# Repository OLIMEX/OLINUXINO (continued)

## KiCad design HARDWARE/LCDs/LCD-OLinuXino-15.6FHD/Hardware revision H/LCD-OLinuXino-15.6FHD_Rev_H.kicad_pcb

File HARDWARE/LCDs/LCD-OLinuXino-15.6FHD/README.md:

# LCD-OLinuXino-15.6FHD

Full HD 15.6 inch display without touchscreen

# Overview

A Full HD (1920x1080) display compatible with A10 and A20 boards.
Due to its high power demand the display is provided with a separate 5V power jack.
Note that it would not work properly with A13 or A10s boards which lack the computational power required for a smooth operation.

# Features

- LCD display 1920x1080 pixels
- 3.5W power consumption
- 15.6”(15.55”)
- HD 16:9 color TFT-LCD with LED backlight
- Works with the more powerful OLinuXino and SOM designs
- Two interface connectors: both 40 pin 0.1" pitch and 40 pin 0.05" pitch
- **Note that the cable to connect to your board and the additional power adapter are sold separately**

# Documents

- [Display datasheet](doc/datasheets/OLIMEX-TFT-LCD-N156HGE-LG1-ver-1-0.pdf)

# Hardware

- [Source files](.)
- [Olimex product page](https://www.olimex.com/Products/OLinuXino/LCD/LCD-OLinuXino-15.6FHD/open-source-hardware)

# FAQ

### What is the difference between LCD-OLinuXino-15.6 and LCD-OLinuXino-15.6FHD?

The dot pitch is different.
The native resolution of LCD-OLinuXino-15.6 is 1366x768.
The native resolution of LCD-OLinuXino-15.6FHD is 1920x1080.

### Which boards can be used with LCD-OLinuXino-15.6FHD?

OLinuXino boards that carry the OLinuXino or SOM name and have an LCD connector would work with the LCD-OLinuXino-15.6FHD.
Unlike the previous iteration of displays, the LCD-OLinuXino-15.6FHD has both 0.1" connector and 0.05" connector on its back.
This allows the easy connection of boards with big LCD connector and also of boards with small LCD connector (like the LIME boards).
You only need a single 40-40 cable with the same step on both sides to connect between the LCD and the board.
Please note that the 15.6 inch display is not recommended for boards with Allwinner A13 or A10s since these boards migth lack the required computing power for a smooth operation (especially under Android).

### I bought LCD-OLinuXino-15.6FHD but when I connect it to the A20-OLinuXino I receive no image on the display. What do I do wrong?

The default A20-OLinuXino image is set for a HDMI display and 720p resolution.
LCD-OLinuXino-15.6FHD has a native resolution of 1920 x 1080 pixels.
To use LCD with A20-OLinuXino you need to set proper video output settings.
Explanation of how to do it can be found at [this wiki article of the A20 board](https://www.olimex.com/wiki/A20-OLinuXino-MICRO#How_to_change_HDMI.2C_VGA_and_LCD_resolutions_in_the_official_Debian_image.3F).

### I bought LCD-OLinuXino-15.6FHD and the SD card that has Linux image written on it. However the resolution I see on my VGA/LCD is not correct. What am I missing?

You would need to change the video output setting using the shell script.
Type: ``./change_display`` and then press **Tab** to auto-complete and press **Enter**.
Navigate to the LCD category and select **1920 x 1080 pixels**.

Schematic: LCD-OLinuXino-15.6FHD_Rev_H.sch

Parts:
C1, C2: 1uF; C_0603_5MIL_DWS
C3, C4, C5, C6, C7, C8, C9, C11, C13, C14, C15, C16, C17, C18, C19, C24: 100nF; C_0402_5MIL_DWS
C10, C12: 33pF; C_0402_5MIL_DWS
C20, C21: 1uF/50V; C_0805_5MIL_DWS
D1, D3: SS34; SMB-KA
D2: BAT54C; SOT23
FB1, FB2, FB3: FB0805; L_0805_5MIL_DWS
FB4: (na) FB0805; L_0805_5MIL_DWS
FET1: IRLML6402; SOT23
IC1: PIC10F206-I/OT; SOT23-6
L1: CL22uH / YS75; SD75
LIME1, LIME2: ML40-GPH127SMT-0X20; GPH127SMT-02X20(PA-V16X-2X20-LF)
P1: CONN_01X40; FPV-WZA21-40-LF
P2: ICSP
PWR1: 5 .. 16V DC; PWR-JACK-MIL-SMT
Q1: 4SB24.000F20E15/5x3.2mm/20ppm/20pF; Q5x3.25
R1, R2, R3, R4, R10: 2.2K; R_0402_5MIL_DWS
R5, R6, R8: 10K; R_0402_5MIL_DWS
R11: 10K; R0402
R12, R15: (na) 100K; R0402
R13: 20K 1%; R_0603_5MIL_DWS
R14: 1.05K 1%; R_0603_5MIL_DWS
RM1: (na); R_MATRIX_4_KICAD
SOM204-LVDS1: FPV-WZA21-40-LF
T1: DTC114YKA(SOT-23); SOT23
U1: MCP1700-1202; SOT89
U2: NCS8801; QFN56_7x7mm_0.4p
U3: MT3608; SOT23-6
eDP1: LCD_CONN; eDP-TERES
uICR1: ML40-GBH-254-SMT-40; GBH-254-SMT-40

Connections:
+1V2: C2.1, C11.1, C17.1, FB2.1, U1.3 (Vo), U2.52 (DVDD12)
+3V3: C1.1, C14.1, C18.1, C24.1, FB1.1, FB3.1, FET1.3, IC1.5, P2.2, R2.1, R5.2, R6.2, R11.1, R15.1, U1.2 (Vi), U2.47 (DVDD33), U2.51 (CSB), U2.55 (I2CSEL), eDP1.1, eDP1.2
/+3.3V: C3.1, FET1.2, LIME1.4, LIME2.3, P1.3, R8.1, SOM204-LVDS1.3, U2.14 (HSVDD33), uICR1.3
/CLK_EDIE: LIME1.30, LIME2.29, SOM204-LVDS1.29, uICR1.29
/CTP_INT: LIME1.38, LIME2.37, RM1.4, SOM204-LVDS1.37, uICR1.37
/D20: LIME1.10, LIME2.9, SOM204-LVDS1.9, uICR1.9
/D21: LIME1.9, LIME2.10, SOM204-LVDS1.10, uICR1.10
/DAT_EDID: LIME1.29, LIME2.30, SOM204-LVDS1.30, uICR1.30
/DCR_EN: LIME1.32, LIME2.31, SOM204-LVDS1.31, uICR1.31
/DP1_N: C5.1, U2.37 (DPO1_N)
/DP1_P: C4.1, U2.38 (DPO1_P)
/DPA_N: C8.1, U2.34 (DPAUX_N)
/DPA_P: C9.1, U2.33 (DPAUX_P)
/DPO_N: C7.1, U2.35 (DPO0_N)
/DPO_P: C6.1, U2.36 (DPO0_P)
/EDP_AUX_N: C8.2, R15.2, eDP1.5
/EDP_AUX_P: C9.2, R12.2, eDP1.4
/EDP_LANE0_N: C6.2, eDP1.8
/EDP_LANE0_P: C7.2, eDP1.7
/EDP_LANE1_N: C4.2, eDP1.11
/EDP_LANE1_P: C5.2, eDP1.10
/GPIO0: LIME1.34, LIME2.33, SOM204-LVDS1.33, uICR1.33
/GPIO1: LIME1.33, LIME2.34, SOM204-LVDS1.34, uICR1.34
/HPD: IC1.6, P1.33, P2.1, R10.1, RM1.5
/HSYNC: P1.29, U2.2 (HSYNC)
/IMG_EN: LIME1.31, LIME2.32, SOM204-LVDS1.32, uICR1.32
/IRES: D2.2 (A), IC1.4, R4.2
/LCD_B0: P1.21, U2.28 (D0)
/LCD_B1: P1.22, U2.27 (D1)
/LCD_B2: P1.23, U2.26 (D2)
/LCD_B3: P1.24, U2.25 (D3)
/LCD_BKL: LIME1.35, LIME2.36, P1.36, SOM204-LVDS1.36, eDP1.15, uICR1.36
/LCD_CLK: P1.31, U2.3 (PCLK)
/LCD_DE: P1.32, U2.56 (DE)
/LCD_PWRE: LIME1.36, LIME2.35, P1.35, SOM204-LVDS1.35, T1.1 (B), uICR1.35
/LVDIE0_N: LIME1.15, LIME2.16, P1.18, SOM204-LVDS1.16, U2.15 (LVDIE0_N), uICR1.16
/LVDIE0_P: LIME1.16, LIME2.15, P1.17, SOM204-LVDS1.15, U2.16 (LVDIE0_P), uICR1.15
/LVDIE1_N: LIME1.17, LIME2.18, P1.16, SOM204-LVDS1.18, U2.17 (LVDIE1_N), uICR1.18
/LVDIE1_P: LIME1.18, LIME2.17, P1.15, SOM204-LVDS1.17, U2.18 (LVDIE1_P), uICR1.17
/LVDIE2_N: LIME1.19, LIME2.20, P1.14, SOM204-LVDS1.20, U2.19 (LVDIE2_N), uICR1.20
/LVDIE2_P: LIME1.20, LIME2.19, P1.13, SOM204-LVDS1.19, U2.20 (LVDIE2_P), uICR1.19
/LVDIE3_N: LIME1.7, LIME2.8, P1.26, SOM204-LVDS1.8, U2.23 (LVDIE3_N), uICR1.8
/LVDIE3_P: LIME1.8, LIME2.7, P1.25, SOM204-LVDS1.7, U2.24 (LVDIE3_P), uICR1.7
/LVDIEC_N: LIME1.5, LIME2.6, P1.28, SOM204-LVDS1.6, U2.21 (LVCIE_N), uICR1.6
/LVDIEC_P: LIME1.6, LIME2.5, P1.27, SOM204-LVDS1.5, U2.22 (LVCIE_P), uICR1.5
/LVDIO0_N: LIME1.21, LIME2.22, P1.12, SOM204-LVDS1.22, U2.4 (LVDIO0_N), uICR1.22
/LVDIO0_P: LIME1.22, LIME2.21, P1.11, SOM204-LVDS1.21, U2.5 (LVDIO0_P), uICR1.21
/LVDIO1_N: LIME1.23, LIME2.24, P1.10, SOM204-LVDS1.24, U2.6 (LVDIO1_N), uICR1.24
/LVDIO1_P: LIME1.24, LIME2.23, P1.9, SOM204-LVDS1.23, U2.7 (LVDIO1_P), uICR1.23
/LVDIO2_N: LIME1.25, LIME2.26, P1.8, SOM204-LVDS1.26, U2.8 (LVDIO2_N), uICR1.26
/LVDIO2_P: LIME1.26, LIME2.25, P1.7, SOM204-LVDS1.25, U2.9 (LVDIO2_P), uICR1.25
/LVDIO3_N: LIME1.13, LIME2.14, P1.20, SOM204-LVDS1.14, U2.12 (LVDIO3_N), uICR1.14
/LVDIO3_P: LIME1.14, LIME2.13, P1.19, SOM204-LVDS1.13, U2.13 (LVDIO3_P), uICR1.13
/LVDIOC_N: LIME1.27, LIME2.28, P1.6, SOM204-LVDS1.28, U2.10 (LVCIO_N), uICR1.28
/LVDIOC_P: LIME1.28, LIME2.27, P1.5, SOM204-LVDS1.27, U2.11 (LVCIO_P), uICR1.27
/NCS_RES: C19.1, D2.3 (K), LIME1.37, LIME2.38, R4.1, RM1.3, SOM204-LVDS1.38, U2.46 (RSTB), uICR1.38
/PIC_RES: P1.37, R10.2, R11.2
/RES: D2.1 (A), P1.34, RM1.6
/SCL: IC1.3, P1.39, P2.5, R6.1, RM1.7, U2.53 (SCL)
/SDA: IC1.1, P1.40, P2.4, R5.1, RM1.8, U2.54 (SDA)
/TWI_SCL: LIME1.40, LIME2.39, RM1.2, SOM204-LVDS1.39, uICR1.39
/TWI_SDA: LIME1.39, LIME2.40, RM1.1, SOM204-LVDS1.40, uICR1.40
/VLEDS: C21.1, D1.1 (K), FB4.2, R13.1, eDP1.21, eDP1.22
/VLED_EN: LIME1.12, LIME2.11, R2.2, SOM204-LVDS1.11, eDP1.14, uICR1.11
/VPWM_EN: LIME1.11, LIME2.12, SOM204-LVDS1.12, uICR1.12
/VSINK: P1.30, U2.1 (VSYNC)
GND: C1.2, C2.2, C3.2, C10.2, C11.2, C12.2, C13.2, C14.2, C15.2, C16.2, C17.2, C18.2, C19.2, C20.2, C21.2, C24.2, IC1.2, LIME1.1, LIME1.3, LIME2.2, LIME2.4, P1.2, P1.4, P1.P1, P1.P2, P2.3, PWR1.2 (-), PWR1.3 (-), R1.1, R12.1, R14.2, SOM204-LVDS1.0, SOM204-LVDS1.2, SOM204-LVDS1.4, T1.2 (E), U1.1 (GND/ADJ), U2.0 (THERMAL), U2.49 (MOSI), U2.50 (SCK), U3.2 (GND), eDP1.0, eDP1.3, eDP1.6, eDP1.9, eDP1.12, eDP1.19, eDP1.20, uICR1.2, uICR1.4
unnamed: C10.1, Q1.1, U2.30 (XTALOUT)
unnamed: C12.1, Q1.2, U2.29 (XTALIN)
unnamed: C13.1, FB1.2, U2.31 (XVDD33)
unnamed: C15.1, FB2.2, U2.43 (AVDD12)
unnamed: C16.1, FB3.2, U2.32 (AVDD33)
unnamed: D1.2 (A), L1.2, U3.1 (OUT)
unnamed: FET1.1, R3.2, R8.2
unnamed: R1.2, U2.45 (PWD)
unnamed: R3.1, T1.3 (C)
unnamed: R13.2, R14.1, U3.3 (FB)
VDD: C20.1, D3.1, FB4.1, L1.1, PWR1.1 (+), U3.4 (EN), U3.5 (IN)

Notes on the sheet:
All lanes impedance 100ohm inter-pair skew < 50mils
eDP
pwm
RGB888
LVDS

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
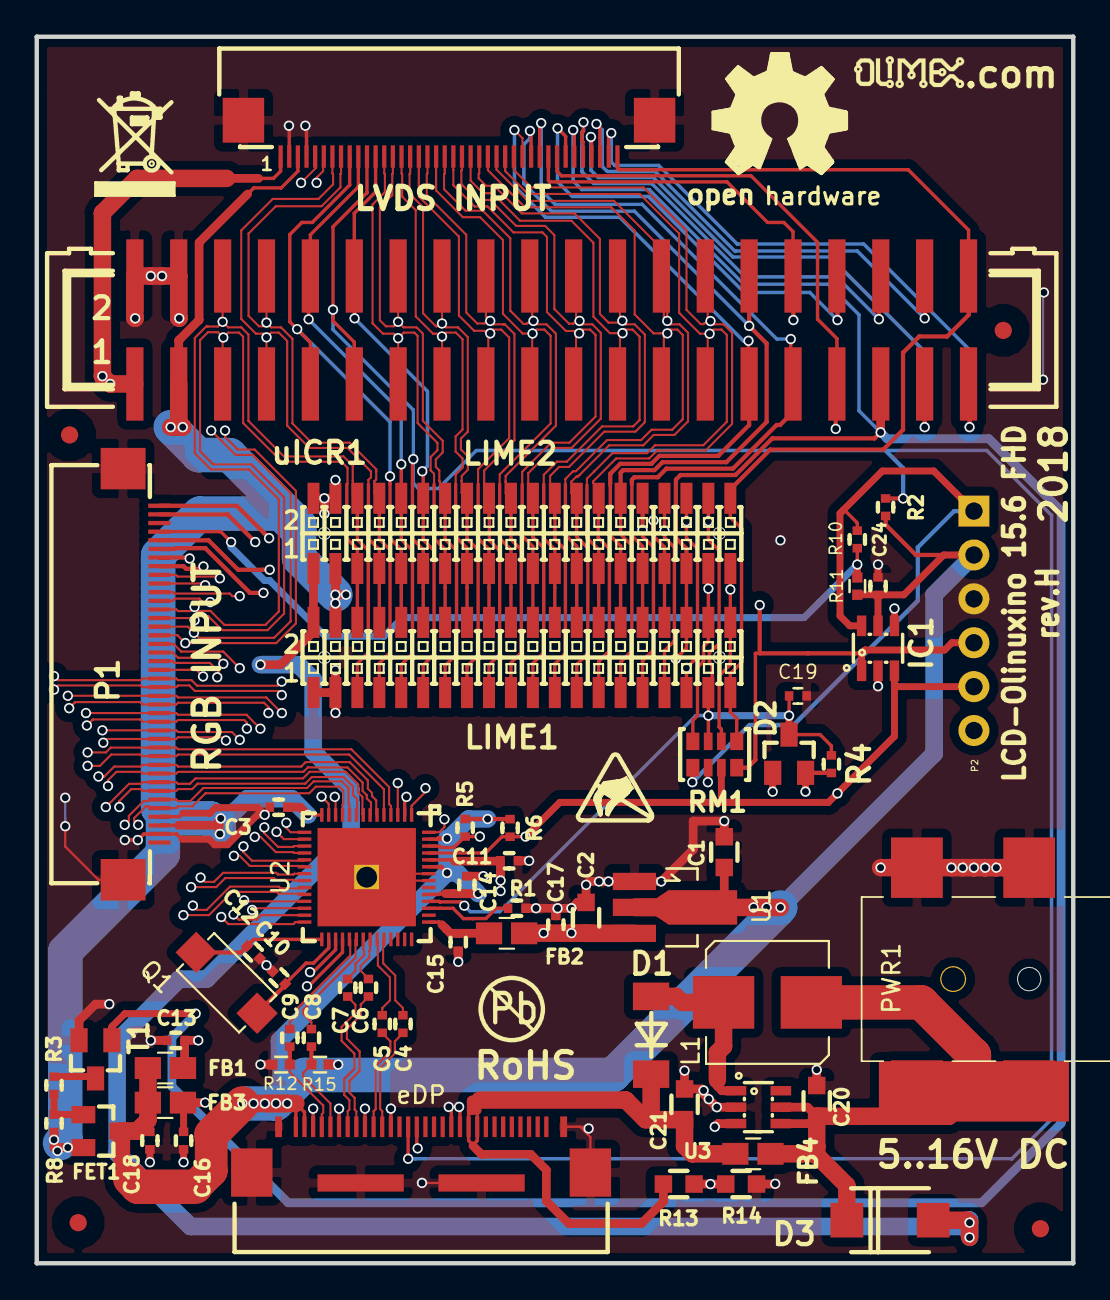
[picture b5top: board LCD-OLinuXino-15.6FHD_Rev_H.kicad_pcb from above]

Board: 4 copper layers, 60.0 x 71.0 mm, 60 parts (0 on the bottom side), 79 nets.

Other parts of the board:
Ref**: Val**; LOGO_ANTISTATIC_SMALL_4.5mmX2.8mm

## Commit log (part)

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2013-08-23 A10-A20-OLinuXino-MICRO REV.C and D
2013-09-05 add video encoding and decoding demo
2013-09-06 iMX233-OLinuXino-NANO CAD files
2013-10-02 Android A20-OLinuXino-TOOLS
2013-10-03 add voice to OLinuXino
2013-10-04 A13-OLinuXino PDF was not searchable
2013-11-23 updated iMX233-OLinuXino-MAXI CAD files to Rev.C2
2013-11-25 Micro schematics in wrong folders.
    Micro revision C in Maxi folders. Needs to be deleted. Lub/OLIMEX
2014-01-21 A10-OLinuXino-LIME REV.B and GPIO description
2014-02-13 A10-OLinuXino-LIME shield templates
2014-02-18 A20-OLinuXino-MICRO REV.E2 upload
2014-04-23 Update DEBIAN-BUILD.txt
    Boot was hanging because terminal in /etc/inittab was ttyAM0 instead of ttyAMA0. Tested on imx nano.
2014-05-27 MOD-IRDA+ code for home automation with OLinuXino
2014-06-18 A10-LIME board revision C files updated
    A10-LIME schematic, board layout and pdf added
2014-07-07 I2C EXAMPLE - MOD-RTC and A20-OLINUXINO-MICRO
    An example of A20-OLINUXINO-MICRO and a RTC module that gets connected
    to the UEXT. Full instructions in the README_RTC_A20.txt
2014-07-23 SPI EXAMPLE - MOD-LCD3310 and A20-OLINUXINO-MICRO
    A demo with detailed description on using the hardware SPI under Debian.
2014-07-25 MOD-RGB firmware 3 demo with A20-OLINUXINO-MICRO
    Detailed instructions might be found in the README.txt file.
2014-07-25 A20 demo examples
2014-07-25 A20 demo examples
    Fixed few paths
2014-08-22 Add Android Jelly Bean build for A13-OLinuXino-WIFI
2014-09-04 Python packages for OLinuXino boards
2014-09-17 iMX233-MICRO revision D files
2014-09-20 Create A20-TOOLS
2014-10-02 A20-OLinuXino-LIME2 hardware sources added
2014-10-23 Added A13 sources
2014-10-24 RT5350F-OLinuXino first prototypes
2014-11-12 Files and description on A20 image compilation
2014-11-14 Torrent to the A20 filesystem
2014-11-19 Formatting improvement of GPIO table for LIME2
2014-12-11 A20-OLinuXino-LIME separated in own folder
2014-12-16 Adding dragon face
2014-12-18 Updated readme of the example
2014-12-23 To load in git formatting
2014-12-23 Updated links to resources need for A20 Debian
2014-12-23 Revert "Update README.txt"
    This reverts commit 9d136c74a2f802c392218a2b047997fe4ff03f86.
2014-12-23 Formatting changes
2014-12-23 Fixed a misleading command in the building doc
2015-01-08 Links to resources updated!
2015-02-24 A13-OLINUXINO files revision G
2015-03-13 revisions
2015-03-16 Updated a number of schematics
2015-03-19 rk3188 datasheet
2015-03-25 Update README.txt
    Modified README( Fixed typo).
2015-04-22 Fix tx DMAs address typo
    This typo cause to hang spidev2 on transfer data in DMA mode.
2015-05-18 RT5350F-OLinuXino update
2015-05-26 RT5350F-OLinuXino-B update
2015-05-27 MOD-IO2 tool
    tool that simplifies the usage of MOD-IO2
2015-05-27 MOD-IO2 Linux tool additional info
2015-05-27 MOD-IO2 Linux tool update
2015-05-27 MOD-IO2 Linux tool
2015-05-28 relay example mod-io2
2015-05-28 MOD-IO2 simple example
2015-05-28 MOD-IO example
2015-05-29 Update to add pwm function
2015-05-29 Update of the pwm function
2015-06-03 Correction of web address
    Correction of small typo in web address.
2015-06-05 Add R8M datasheet
2015-06-09 a13 build description
2015-06-09 torrent
2015-06-09 added build description
2015-06-11 updated readme.txt
2015-06-15 Fix pyA20 gpio1 connector constants
    In definition of gpio1 connector mapping constant there is a "cut&paste" error which prevent access to port pins.
2015-06-19 Add C++ library for GPIOs
2015-06-30 pyA13 increased minor revision
2015-07-06 Updated olinuxino-rt5350 firmware image
2015-08-15 Initial version adding eMMC support
    This commit creates a rev D board with an optional eMMC variant for
    storage.
    Some notes:
    The eMMC chip generally handles the state internally when enabling
    4 or 8 bit data modes. So having the spare data lines connected to
    NDQ[4:7] should be no problem. This needs to be tested however and
2015-08-17 Updated system images
2015-08-17 Fixed typo
2015-08-23 Re-route Sata power enable pins
    With this patch, we re-route the sata power enable pins around to avoid
    being in the NAND flash area, potentially freeing up space for other
    purposes (eMMC) here.
    This patch unfortunately has some noise in it (diff-ing eagle files is
    hard)
    Noise 1: Started to use eagle 7.2
2015-08-23 Move sata lines slightly north to make more room below the NAND flash
2015-08-23 Rename R28 to NAND_WP
    R28 is a spot where a zero ohm resistor can be placed to control the
    NAND flash's Write Protect. This commit renames this resistor to NAND_WP
    and marks it as such on the silk-screen.
2015-08-24 Updated release image
2015-11-02 New builds
    Jessie build instructions
2015-11-04 New defconfig
2015-11-04 Update instructions
2015-11-10 Added change display script
    For reference only, it is also inside the file system, no need to
    download it separately.
2015-11-10 Fixed RT5350 issue with repeating MAC address
2015-11-10 RT5350 README updated
2015-11-13 H3-OLinuXino prototype CAD files and H3 SoC datasheet
2015-11-17 A33-OLinuXino first prototypes update CAD files
2015-11-20 A64-OLinuXino component placement, all components libraries updated
2016-01-03 Fixed minor detail in fdisk commands
2016-01-07 Update
    Fixed bug in GPIO3 and GPIO4
2016-01-22 A64-OLinuXino routing completed
2016-01-29 Revision C
    Minor changes mainly on the I2C lines (set to hardware I2C).
2016-03-03 Added image for RT5350F-OLinuXino-DIN
2016-04-08 New A20 releases
2016-04-08 Link to FS torrent
2016-04-11 Update
    Incorrect bit swap
2016-04-20 Fixes raw downloads
    The script.bin and uEnv.txt files should be downloaded raw;
    the current wget command downloads the HTML page instead of the desired file.
2016-04-20 Incorrect copy command
    At this point the file is called `uEnv.txt`, not `uEnv.txt.bin`
2016-06-17 Updated instructions
    Build description updated, RAM now 384MHz to improve stability.
2016-06-17 Update
    Added examples for MOD-IO2 and MOD-LED8x8RGB
2016-06-17 Renamed README file
2016-06-17 Update
    Removed duplicate folder for the MOD-IO2 example (the other one is
    located inside UEXT-MODULES folder)
2016-06-23 A20-OLinuXino-LIME2 Rev. F and Rev.G update
2016-07-05 Update text wrapping
2016-07-05 Update names
2016-07-08 Update and formatting
2016-07-08 updated links to be raw
2016-07-12 Update
    Updated description for booting from eMMC
2016-08-31 Update
    Added demo example for A10-OLinuXino-LIME and MOD-IO2 (with
    A10-OLinuXino-LIME-UEXT) via I2C interface.
2016-09-02 Revert "Update"
    This reverts commit e85321694b9b064cff2fa52dd0ea86b82c493002.
2016-09-02 Revert "Revert "Update""
    This reverts commit dbac98d0b39abfff813d94a6c430e85e8013d58c.
2016-09-05 Update
    README.md file formatted to be easier to read (no changes on the content itself).
2016-09-06 Build instructions A33
    Update
2016-09-06 A33 build instructions
    Update
2016-09-22 Fix
    Created by mistake
2016-10-03 Fix DDR hang
2016-10-13 new patch applied for emmc
2016-10-20 add revision_changes to LIME2, upload A64-OLinuXino-Rev.B
2016-10-20 update RT5350F-OLinuXino Rev.D and revision changes
2016-10-28 Update
    New patch that applies workaround for GbE issues and ensures DDR clock
    is set to 384MHz for all A20 boards
2016-10-28 update
    production release files
2016-11-15 Revert "Update README.md"
    This reverts commit 83be10e186a07deceefdad44364be99a773476df.
2016-11-15 Revert "Revert "Update README.md""
    This reverts commit dd3e832a58712f4e790abab346b99f2f3f6217ad.
2016-11-16 Updated images with fixed factory partition
2016-12-10 64k eeprom...
2016-12-14 update
    changed factory eeprom with better settings; relocated files to non-ssl
    location for easier access
2017-01-30 update
    the text file contains information about the interfaces tested and the
    common practices when using the official image
2017-02-06 Updated debian readme.txt file location
2017-02-16 Small typo
2017-03-31 update
    uploaded last two schematics searchable
2017-04-07 New releases patches
2017-04-07 new scripts
2017-04-18 update
    New hardware revisions and new board variants (industrial; EMMC;
    industrial + EMMC)
2017-04-18 update
    hardware changes from revision G to revision J
2017-06-06 A64-OLinuXino Rev.C update
2017-06-16 update
    changed archive format from from 7z to tgz
2017-07-05 update
    fixes for port e powering
2017-08-21 new releases
2017-08-23 updated instructions
2017-11-07 New commit
    displays sources and exports
2017-11-23 update
    fixed and improved hardware revision changes
2017-12-04 Uptade
    EEPROM contents description
2018-03-01 RTC-MOD Fix
    if year not leap return wrong day
    if sync on 01-03-2018 Sync_RTC return 29-02-2018
2018-03-02 Not year leap bug fix
    use:
    python MOD-RTC.py -i 2 -b 1 -t 'Europe/Sofia' -r
    local time zone is not finish
2018-03-04 Fix 29-02 on not leap year, add timezone
    python RTC-MOD.py -b 1 -t Europe/Sofia -i 2 -r
2018-03-30 Update
    Message about Commercial/Industrial grade more informative now (showing the range of degrees IN CELSIUS).
2018-04-11 update
    Hardware revision H
2018-07-18 Pretty READMEs with improved grammar
2018-07-18 Minor doc formatting
2018-07-18 Fix format
2018-07-18 Reorganize A10S files to make documentation much easier
2018-07-18 Reorganize A13 files to make documentation much easier
2018-07-18 Add A20 landing page
2018-07-19 Reorganize A31 & H3 files to make documentation much easier
2018-07-19 Reorganize A33 & A64 files to make documentation much easier
2018-07-19 Reorganize iMX233 files to make documentation much easier
2018-07-19 Reorganize RK3066 files to make documentation much easier
2018-07-19 Reorganize RK3188 files to make documentation much easier
2018-07-19 Reorganize A20-GPIO files to make documentation much easier
2018-07-19 Reorganize Python files to make documentation much easier
2018-07-19 Reorganize UEXT files to make documentation much easier
2018-07-19 Move miscellaneous files into their own directory
2018-07-19 Clean up root directory
2018-09-25 Update
    Latest hardware revisions
2018-09-25 Update
    new schematics
2018-10-01 Update
    Added hw changelog for A33 design
2018-11-30 Update
    torrents
2018-11-30 Update
    Torrent links
2018-12-13 Fix
    Small fixes thanks to jcalfee
2018-12-17 Update
    New release
2019-01-08 Create product pages/documentation; improve format
2019-01-16 Updated
    15.6FHD latest hardware revision
2019-01-16 Update
    Description updated 15.6 displays
2019-02-25 Update
    added latest version of the eeprom contents
2019-04-05 spelling fixes
2019-04-09 Update
    Latest hardware revison I1 for A10/20 LIME
2019-07-02 Update
    Major re-organization
2019-07-08 Update
    Update
2019-07-16 New software
    Added GTK
2019-09-12 Update
    Comment
2019-12-17 fix corrupted RK3066 PDFs
2020-03-31 Update
    New revison LCD guide
2020-04-01 upload LIME2-SERVER user manual
2020-05-13 add LIME2 plastic box stl files
2020-05-20 Update
    revision changes
2020-05-20 Update
    revisions L2 and M
2020-11-16 Update BUILD_DESCRIPTION_A20_Olimex_kernel_3.4.103+_Jessie_rel_8.txt
    Updated links to olimex branch
2021-03-23 Update
    Revision G files and change log
2021-04-02 Update README.md
    formatting
2021-06-21 Lime2-SATA
    Update
2021-06-23 Update
    new document revision
2021-10-07 add STMP157-OLinuXino-LIME2
2021-10-07 3d view components fixed
2022-01-07 Update
    released revision D of Olimage guide
2022-02-25 Added README
2022-07-06 Update
    Added I2 and I3 revisions files and updated the revision changes text document
2023-02-27 Update
    Links updated
2023-04-25 README rewrite
2023-10-04 Update
    A13-OLinuXino-MICRO revisions C design files
2024-07-17 readme update
2024-07-26 Update modio2tool
2024-09-11 Update
    Added revision N
